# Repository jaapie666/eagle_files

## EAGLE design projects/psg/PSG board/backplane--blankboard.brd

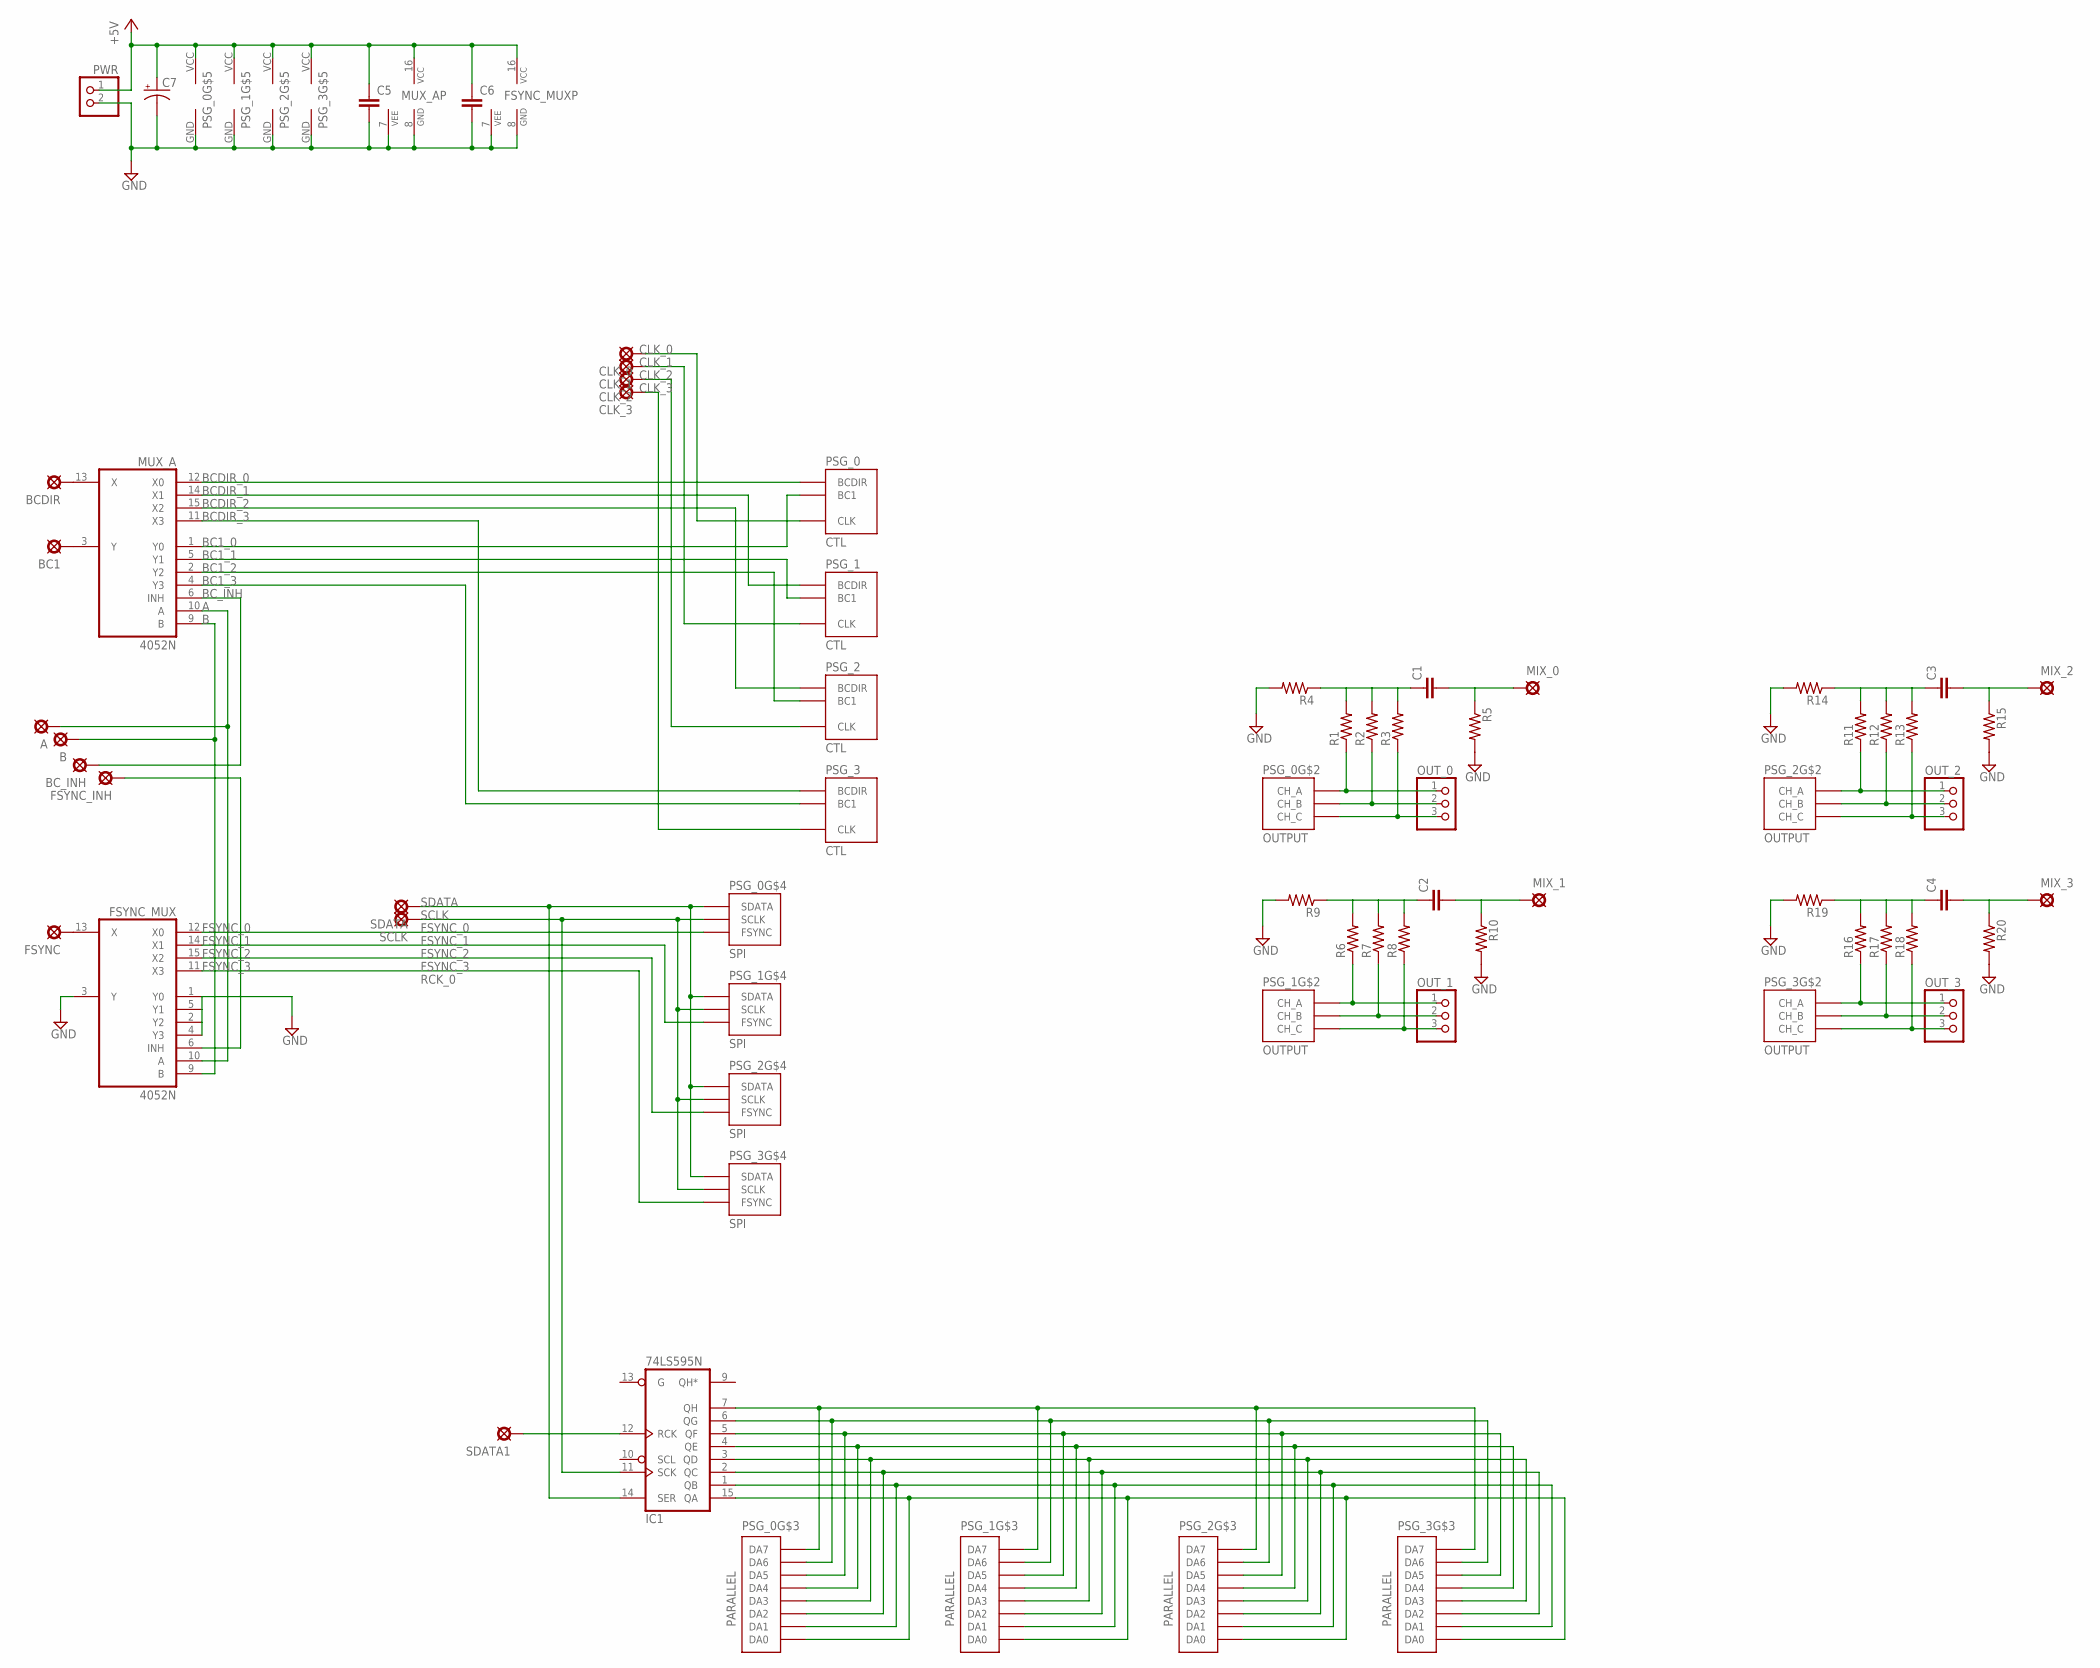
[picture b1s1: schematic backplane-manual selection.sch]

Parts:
A: PAD; SQUARE
B: PAD; SQUARE
BC1: PAD; SQUARE
BCDIR: PAD; SQUARE
BC_INH: PAD; SQUARE
C1, C2, C3, C4: 080X0452; 080X045
C5, C6: 050X030_0251; 050X030_025
C7: 0631; 063_025
CLK_0, CLK_1, CLK_2, CLK_3: PAD; SQUARE
FSYNC: PAD; SQUARE
FSYNC_INH: PAD; SQUARE
FSYNC_MUX: 4052N; DIL16
IC1: 74LS595N; DIL16
MIX_0, MIX_1, MIX_2, MIX_3: PAD; SQUARE
MUX_A: 4052N; DIL16
OUT_0, OUT_1, OUT_2, OUT_3: PINHD-1X3; 1X03
PSG_0, PSG_1, PSG_2, PSG_3: PSG_DAUGHTER
PWR: PINHD-1X2; 1X02
R1, R2, R3, R4, R5, R6, R7, R8, R9, R10, R11, R12, R13, R14, R15, R16, R17, R18, R19, R20: 6MM.3; R0207/3
SCLK: PAD; SQUARE
SDATA, SDATA1: PAD; SQUARE

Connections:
+5V: C5.1, C6.1, C7.+, FSYNC_MUX.16 (VCC), MUX_A.16 (VCC), PSG_0.VCC, PSG_1.VCC, PSG_2.VCC, PSG_3.VCC, PWR.1; also elsewhere on the board
A: A.1, FSYNC_MUX.10 (A), MUX_A.10 (A); also elsewhere on the board
B: B.1, FSYNC_MUX.9 (B), MUX_A.9 (B); also elsewhere on the board
BC1_0: MUX_A.1 (Y0), PSG_0.BC1; also elsewhere on the board
BC1_1: MUX_A.5 (Y1), PSG_1.BC1; also elsewhere on the board
BC1_2: MUX_A.2 (Y2), PSG_2.BC1; also elsewhere on the board
BC1_3: MUX_A.4 (Y3), PSG_3.BC1; also elsewhere on the board
BCDIR_0: MUX_A.12 (X0), PSG_0.BCDIR; also elsewhere on the board
BCDIR_1: MUX_A.14 (X1), PSG_1.BCDIR; also elsewhere on the board
BCDIR_2: MUX_A.15 (X2), PSG_2.BCDIR; also elsewhere on the board
BCDIR_3: MUX_A.11 (X3), PSG_3.BCDIR; also elsewhere on the board
BC_INH: BC_INH.1, MUX_A.6 (INH); also elsewhere on the board
CLK_0: CLK_0.1, PSG_0.CLK
CLK_1: CLK_1.1, PSG_1.CLK
CLK_2: CLK_2.1, PSG_2.CLK
CLK_3: CLK_3.1, PSG_3.CLK
FSYNC: FSYNC.1, FSYNC_MUX.13 (X)
FSYNC_0: FSYNC_MUX.12 (X0), PSG_0.FSYNC
FSYNC_1: FSYNC_MUX.14 (X1), PSG_1.FSYNC
FSYNC_2: FSYNC_MUX.15 (X2), PSG_2.FSYNC
FSYNC_3: FSYNC_MUX.11 (X3), PSG_3.FSYNC
FSYNC_INH: FSYNC_INH.1, FSYNC_MUX.6 (INH)
GND: C5.2, C6.2, C7.-, FSYNC_MUX.1 (Y0), FSYNC_MUX.2 (Y2), FSYNC_MUX.3 (Y), FSYNC_MUX.4 (Y3), FSYNC_MUX.5 (Y1), FSYNC_MUX.7 (VEE), FSYNC_MUX.8 (GND), IC1.8 (GND), MUX_A.7 (VEE), MUX_A.8 (GND), PSG_0.GND, PSG_1.GND, PSG_2.GND, PSG_3.GND, PWR.2, R4.2, R5.2, R9.2, R10.2, R14.2, R15.2, R19.2, R20.2; also elsewhere on the board
unnamed: C1.1, R1.2, R2.2, R3.2, R4.1
unnamed 24: BCDIR.1, MUX_A.13 (X); also elsewhere on the board
unnamed 25: BC1.1, MUX_A.3 (Y); also elsewhere on the board
unnamed: C1.2, MIX_0.1, R5.1
unnamed: C2.1, R6.2, R7.2, R8.2, R9.1
unnamed: C2.2, MIX_1.1, R10.1
unnamed: C3.1, R11.2, R12.2, R13.2, R14.1
unnamed: C3.2, MIX_2.1, R15.1
unnamed 31: IC1.7 (QH), PSG_0.DA7, PSG_1.DA7, PSG_2.DA7, PSG_3.DA7; also elsewhere on the board
unnamed 32: IC1.15 (QA), PSG_0.DA0, PSG_1.DA0, PSG_2.DA0, PSG_3.DA0; also elsewhere on the board
unnamed 33: IC1.1 (QB), PSG_0.DA1, PSG_1.DA1, PSG_2.DA1, PSG_3.DA1; also elsewhere on the board
unnamed 34: IC1.2 (QC), PSG_0.DA2, PSG_1.DA2, PSG_2.DA2, PSG_3.DA2; also elsewhere on the board
unnamed 35: IC1.3 (QD), PSG_0.DA3, PSG_1.DA3, PSG_2.DA3, PSG_3.DA3; also elsewhere on the board
unnamed 36: IC1.4 (QE), PSG_0.DA4, PSG_1.DA4, PSG_2.DA4, PSG_3.DA4; also elsewhere on the board
unnamed 37: IC1.5 (QF), PSG_0.DA5, PSG_1.DA5, PSG_2.DA5, PSG_3.DA5; also elsewhere on the board
unnamed 38: IC1.6 (QG), PSG_0.DA6, PSG_1.DA6, PSG_2.DA6, PSG_3.DA6; also elsewhere on the board
unnamed: OUT_0.1, PSG_0.OUT_A (CH_A), R1.1
unnamed: OUT_0.2, PSG_0.OUT_B (CH_B), R2.1
unnamed: OUT_0.3, PSG_0.OUT_C (CH_C), R3.1
unnamed: OUT_1.1, PSG_1.OUT_A (CH_A), R6.1
unnamed: OUT_1.2, PSG_1.OUT_B (CH_B), R7.1
unnamed: OUT_1.3, PSG_1.OUT_C (CH_C), R8.1
unnamed: OUT_2.1, PSG_2.OUT_A (CH_A), R11.1
unnamed: OUT_2.2, PSG_2.OUT_B (CH_B), R12.1
unnamed: OUT_2.3, PSG_2.OUT_C (CH_C), R13.1
unnamed: OUT_3.1, PSG_3.OUT_A (CH_A), R16.1
unnamed: OUT_3.2, PSG_3.OUT_B (CH_B), R17.1
unnamed: OUT_3.3, PSG_3.OUT_C (CH_C), R18.1
unnamed: C4.1, R16.2, R17.2, R18.2, R19.1
unnamed: C4.2, MIX_3.1, R20.1
RCK_0: IC1.12 (RCK), SDATA1.1
SCLK: IC1.11 (SCK), PSG_0.SCLK, PSG_1.SCLK, PSG_2.SCLK, PSG_3.SCLK, SCLK.1
SDATA: IC1.14 (SER), PSG_0.SDATA, PSG_1.SDATA, PSG_2.SDATA, PSG_3.SDATA, SDATA.1
VCC: IC1.16 (VCC)

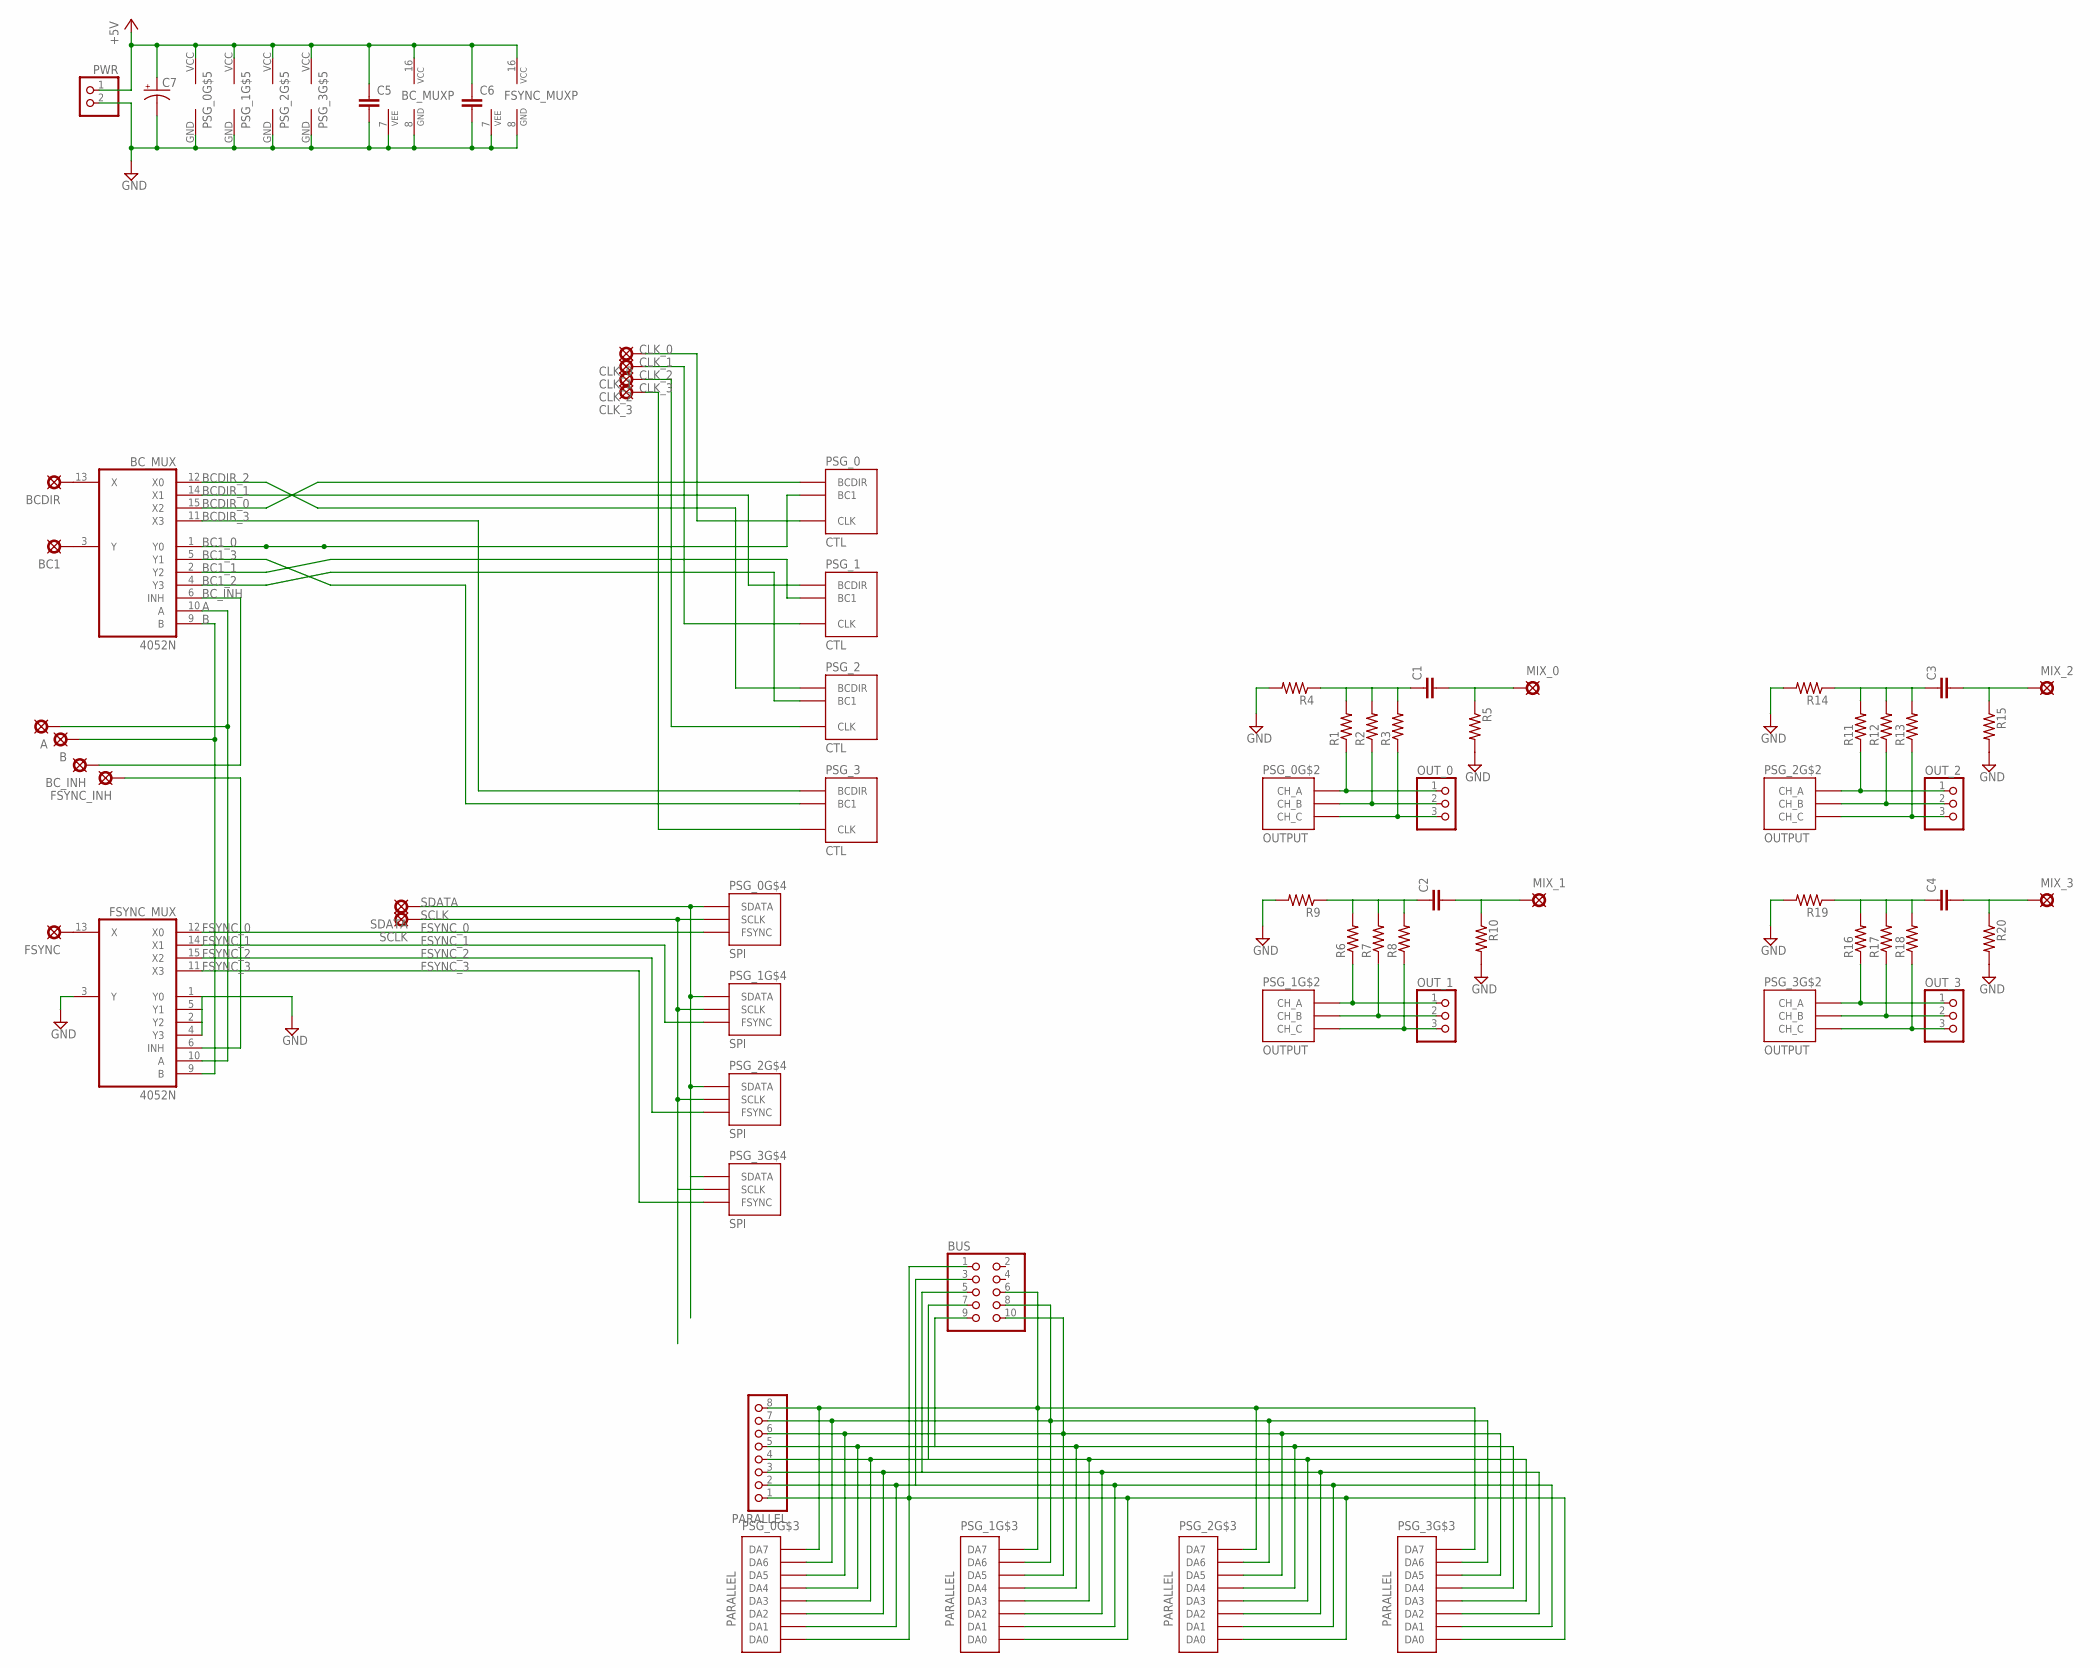
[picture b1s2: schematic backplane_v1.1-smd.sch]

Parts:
A: PAD; SQUARE
B: PAD; SQUARE
BC1: PAD; SQUARE
BCDIR: PAD; SQUARE
BC_INH: PAD; SQUARE
BC_MUX: 4052N; DIL16
BUS: PINHD-2X5IDC; 10PIN_IDC
C1, C2, C3, C4: 070X0302; 070X030
C5, C6: 050X030_0251; 050X030_025
C7: 0631; 063_025
CLK_0, CLK_1, CLK_2, CLK_3: PAD; SQUARE
FSYNC: PAD; SQUARE
FSYNC_INH: PAD; SQUARE
FSYNC_MUX: 4052N; DIL16
MIX_0, MIX_1, MIX_2, MIX_3: PAD; SQUARE
OUT_0, OUT_1, OUT_2, OUT_3: PINHD-1X3; 1X03
PARALLEL: PINHD-1X8; 1X08
PSG_0, PSG_1, PSG_2, PSG_3: PSG_DAUGHTER
PWR: PINHD-1X2; 1X02
R1, R2, R3, R4, R5, R6, R7, R8, R9, R10, R11, R12, R13, R14, R15, R16, R17, R18, R19, R20: 6MM.3; R0207/3
SCLK: PAD; SQUARE
SDATA: PAD; SQUARE

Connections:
+5V: BC_MUX.16 (VCC), C5.1, C6.1, C7.+, FSYNC_MUX.16 (VCC), PSG_0.VCC, PSG_1.VCC, PSG_2.VCC, PSG_3.VCC, PWR.1; also elsewhere on the board
A: A.1, BC_MUX.10 (A), FSYNC_MUX.10 (A); also elsewhere on the board
B: B.1, BC_MUX.9 (B), FSYNC_MUX.9 (B); also elsewhere on the board
BC1_0: BC_MUX.1 (Y0), PSG_0.BC1; also elsewhere on the board
BC1_1: BC_MUX.2 (Y2), PSG_1.BC1; also elsewhere on the board
BC1_2: BC_MUX.4 (Y3), PSG_2.BC1; also elsewhere on the board
BC1_3: BC_MUX.5 (Y1), PSG_3.BC1; also elsewhere on the board
BCDIR_0: BC_MUX.15 (X2), PSG_0.BCDIR; also elsewhere on the board
BCDIR_1: BC_MUX.14 (X1), PSG_1.BCDIR; also elsewhere on the board
BCDIR_2: BC_MUX.12 (X0), PSG_2.BCDIR; also elsewhere on the board
BCDIR_3: BC_MUX.11 (X3), PSG_3.BCDIR; also elsewhere on the board
BC_INH: BC_INH.1, BC_MUX.6 (INH); also elsewhere on the board
CLK_0: CLK_0.1, PSG_0.CLK
CLK_1: CLK_1.1, PSG_1.CLK
CLK_2: CLK_2.1, PSG_2.CLK
CLK_3: CLK_3.1, PSG_3.CLK
FSYNC: FSYNC.1, FSYNC_MUX.13 (X)
FSYNC_0: FSYNC_MUX.12 (X0), PSG_0.FSYNC
FSYNC_1: FSYNC_MUX.14 (X1), PSG_1.FSYNC
FSYNC_2: FSYNC_MUX.15 (X2), PSG_2.FSYNC
FSYNC_3: FSYNC_MUX.11 (X3), PSG_3.FSYNC
FSYNC_INH: FSYNC_INH.1, FSYNC_MUX.6 (INH)
GND: BC_MUX.7 (VEE), BC_MUX.8 (GND), C5.2, C6.2, C7.-, FSYNC_MUX.1 (Y0), FSYNC_MUX.2 (Y2), FSYNC_MUX.3 (Y), FSYNC_MUX.4 (Y3), FSYNC_MUX.5 (Y1), FSYNC_MUX.7 (VEE), FSYNC_MUX.8 (GND), PSG_0.GND, PSG_1.GND, PSG_2.GND, PSG_3.GND, PWR.2, R4.2, R5.2, R9.2, R10.2, R14.2, R15.2, R19.2, R20.2; also elsewhere on the board
unnamed: C1.1, R1.2, R2.2, R3.2, R4.1
unnamed 24: BCDIR.1, BC_MUX.13 (X); also elsewhere on the board
unnamed 25: BC1.1, BC_MUX.3 (Y); also elsewhere on the board
unnamed: C1.2, MIX_0.1, R5.1
unnamed: C2.1, R6.2, R7.2, R8.2, R9.1
unnamed: C2.2, MIX_1.1, R10.1
unnamed: C3.1, R11.2, R12.2, R13.2, R14.1
unnamed: C3.2, MIX_2.1, R15.1
unnamed 31: BUS.6, PARALLEL.8, PSG_0.DA7, PSG_1.DA7, PSG_2.DA7, PSG_3.DA7; also elsewhere on the board
unnamed 32: BUS.1, PARALLEL.1, PSG_0.DA0, PSG_1.DA0, PSG_2.DA0, PSG_3.DA0; also elsewhere on the board
unnamed 33: BUS.3, PARALLEL.2, PSG_0.DA1, PSG_1.DA1, PSG_2.DA1, PSG_3.DA1; also elsewhere on the board
unnamed 34: BUS.5, PARALLEL.3, PSG_0.DA2, PSG_1.DA2, PSG_2.DA2, PSG_3.DA2; also elsewhere on the board
unnamed 35: BUS.7, PARALLEL.4, PSG_0.DA3, PSG_1.DA3, PSG_2.DA3, PSG_3.DA3; also elsewhere on the board
unnamed 36: BUS.9, PARALLEL.5, PSG_0.DA4, PSG_1.DA4, PSG_2.DA4, PSG_3.DA4; also elsewhere on the board
unnamed 37: BUS.10, PARALLEL.6, PSG_0.DA5, PSG_1.DA5, PSG_2.DA5, PSG_3.DA5; also elsewhere on the board
unnamed 38: BUS.8, PARALLEL.7, PSG_0.DA6, PSG_1.DA6, PSG_2.DA6, PSG_3.DA6; also elsewhere on the board
unnamed: OUT_0.1, PSG_0.OUT_A (CH_A), R1.1
unnamed: OUT_0.2, PSG_0.OUT_B (CH_B), R2.1
unnamed: OUT_0.3, PSG_0.OUT_C (CH_C), R3.1
unnamed: OUT_1.1, PSG_1.OUT_A (CH_A), R6.1
unnamed: OUT_1.2, PSG_1.OUT_B (CH_B), R7.1
unnamed: OUT_1.3, PSG_1.OUT_C (CH_C), R8.1
unnamed: OUT_2.1, PSG_2.OUT_A (CH_A), R11.1
unnamed: OUT_2.2, PSG_2.OUT_B (CH_B), R12.1
unnamed: OUT_2.3, PSG_2.OUT_C (CH_C), R13.1
unnamed: OUT_3.1, PSG_3.OUT_A (CH_A), R16.1
unnamed: OUT_3.2, PSG_3.OUT_B (CH_B), R17.1
unnamed: OUT_3.3, PSG_3.OUT_C (CH_C), R18.1
unnamed: C4.1, R16.2, R17.2, R18.2, R19.1
unnamed: C4.2, MIX_3.1, R20.1
SCLK: PSG_0.SCLK, PSG_1.SCLK, PSG_2.SCLK, PSG_3.SCLK, SCLK.1; also elsewhere on the board
SDATA: PSG_0.SDATA, PSG_1.SDATA, PSG_2.SDATA, PSG_3.SDATA, SDATA.1; also elsewhere on the board

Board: 2 copper layers, 57 parts (0 on the bottom side), 56 nets, no tracks yet.

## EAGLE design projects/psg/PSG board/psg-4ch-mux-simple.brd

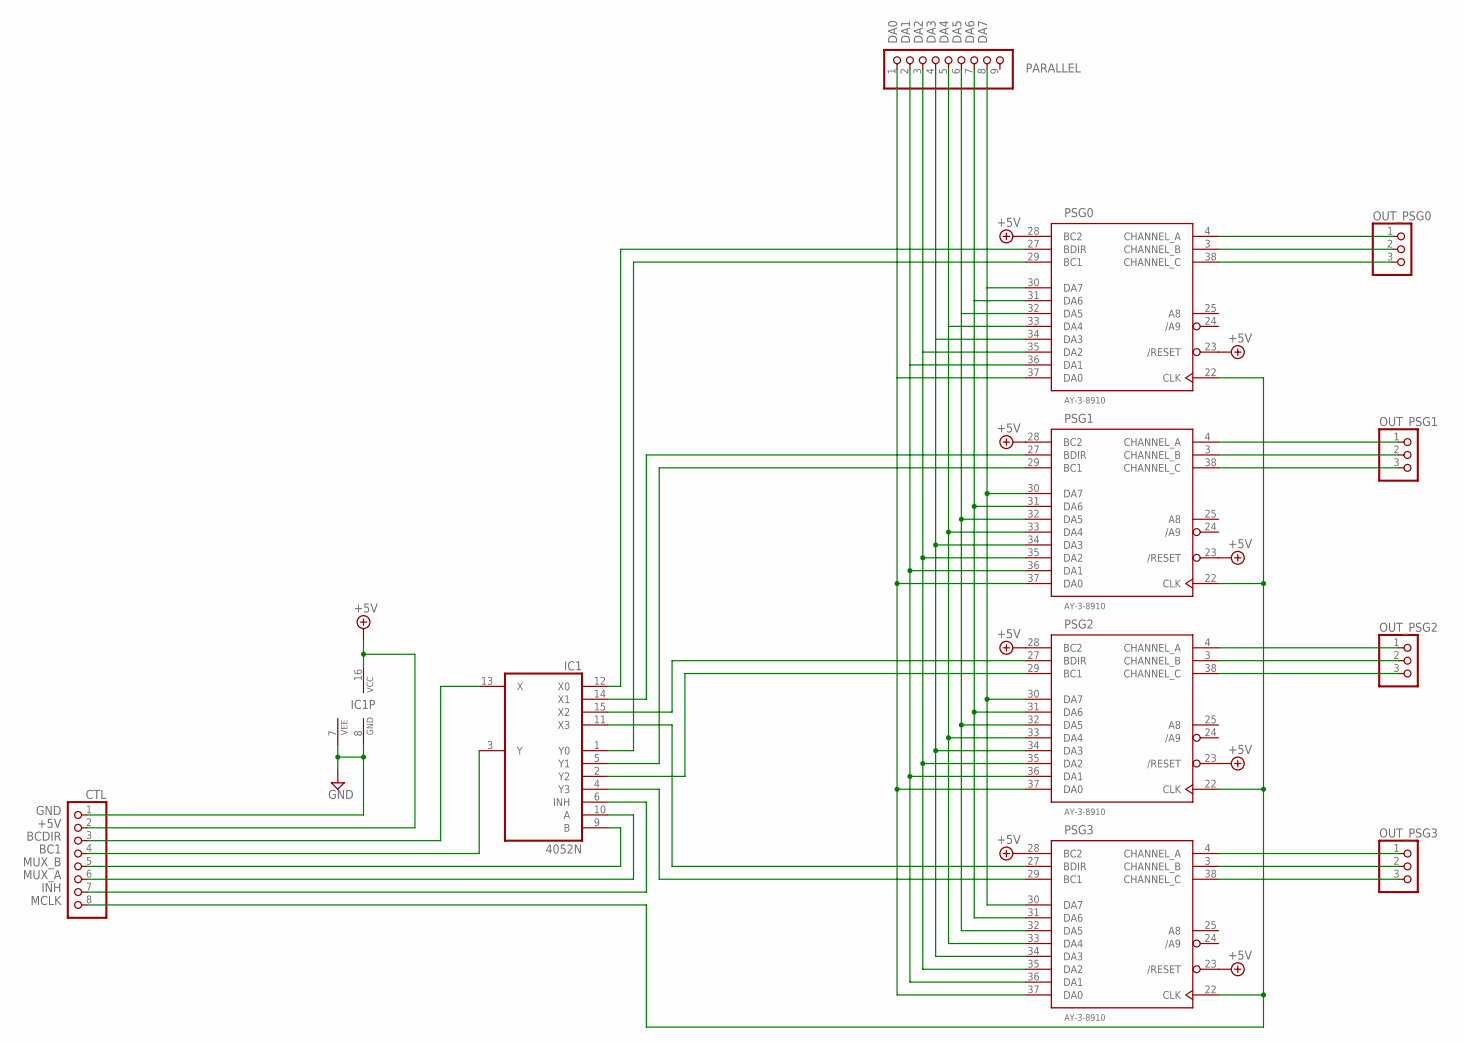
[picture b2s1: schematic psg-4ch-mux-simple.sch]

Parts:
CTL: PINHD-1X8; 1X08
IC1: 4052N; DIL16
OUT_PSG0, OUT_PSG1, OUT_PSG2, OUT_PSG3: PINHD-1X3; 1X03
PARALLEL: PINHD-1X9; 1X09
PSG0, PSG1, PSG2, PSG3: AY-3-8910(2); DIL-40

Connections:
+5V: CTL.2, IC1.16 (VCC), PSG0.23 (/RESET), PSG0.28 (BC2), PSG1.23 (/RESET), PSG1.28 (BC2), PSG2.23 (/RESET), PSG2.28 (BC2), PSG3.23 (/RESET), PSG3.28 (BC2)
+V: PSG0.40 (+V), PSG1.40 (+V), PSG2.40 (+V), PSG3.40 (+V)
BC1: CTL.4, IC1.3 (Y)
BC1_0: IC1.1 (Y0), PSG0.29 (BC1)
BC1_1: IC1.5 (Y1), PSG1.29 (BC1)
BC1_2: IC1.2 (Y2), PSG2.29 (BC1)
BC1_3: IC1.4 (Y3), PSG3.29 (BC1)
BCDIR: CTL.3, IC1.13 (X)
BCDIR_0: IC1.12 (X0), PSG0.27 (BDIR)
BCDIR_1: IC1.14 (X1), PSG1.27 (BDIR)
BCDIR_2: IC1.15 (X2), PSG2.27 (BDIR)
BCDIR_3: IC1.11 (X3), PSG3.27 (BDIR)
DA0: PARALLEL.1, PSG0.37 (DA0)
DA1: PARALLEL.2, PSG0.36 (DA1)
DA2: PARALLEL.3, PSG0.35 (DA2)
DA3: PARALLEL.4, PSG0.34 (DA3)
DA4: PARALLEL.5, PSG0.33 (DA4)
DA5: PARALLEL.6, PSG0.32 (DA5)
DA6: PARALLEL.7, PSG0.31 (DA6)
DA7: PARALLEL.8, PSG0.30 (DA7)
DA8: PSG3.37 (DA0)
DA9: PSG3.36 (DA1)
DA10: PSG3.35 (DA2)
DA11: PSG3.34 (DA3)
DA12: PSG3.33 (DA4)
DA13: PSG3.32 (DA5)
DA14: PSG3.31 (DA6)
DA15: PSG3.30 (DA7)
GND: CTL.1, IC1.7 (VEE), IC1.8 (GND), PSG0.1 (GND), PSG1.1 (GND), PSG2.1 (GND), PSG3.1 (GND)
INH: CTL.7, IC1.6 (INH)
MCLK: CTL.8, PSG0.22 (CLK), PSG1.22 (CLK), PSG2.22 (CLK), PSG3.22 (CLK)
MUX_A: CTL.6, IC1.10 (A)
MUX_B: CTL.5, IC1.9 (B)
unnamed: OUT_PSG0.1, PSG0.4 (CHANNEL_A)
unnamed: OUT_PSG0.2, PSG0.3 (CHANNEL_B)
unnamed: OUT_PSG0.3, PSG0.38 (CHANNEL_C)
unnamed: OUT_PSG1.1, PSG1.4 (CHANNEL_A)
unnamed: OUT_PSG1.2, PSG1.3 (CHANNEL_B)
unnamed: OUT_PSG1.3, PSG1.38 (CHANNEL_C)
unnamed: OUT_PSG2.1, PSG2.4 (CHANNEL_A)
unnamed: OUT_PSG2.2, PSG2.3 (CHANNEL_B)
unnamed: OUT_PSG2.3, PSG2.38 (CHANNEL_C)
unnamed: OUT_PSG3.1, PSG3.4 (CHANNEL_A)
unnamed: OUT_PSG3.2, PSG3.3 (CHANNEL_B)
unnamed: OUT_PSG3.3, PSG3.38 (CHANNEL_C)

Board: 2 copper layers, 11 parts (0 on the bottom side), 37 nets, no tracks yet.

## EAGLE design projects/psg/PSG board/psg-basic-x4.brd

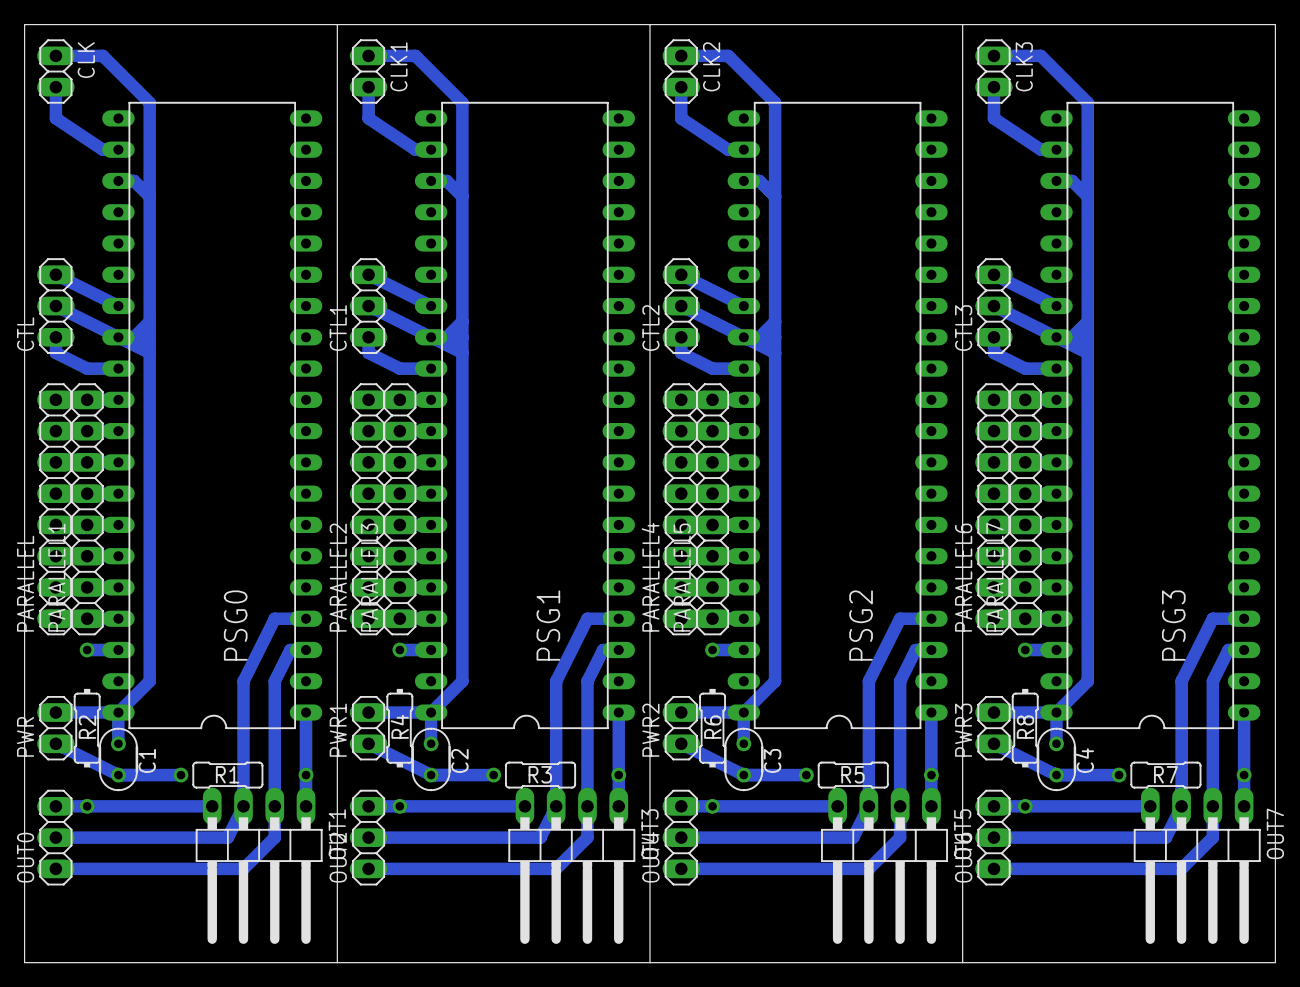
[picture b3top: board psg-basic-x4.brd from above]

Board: 2 copper layers, 101.6 x 76.2 mm, 44 parts (0 on the bottom side), 72 nets.

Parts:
C1, C2, C3, C4: 100n; 050X030_025
CLK, CLK1, CLK2, CLK3: 1X02
CTL, CTL1, CTL2, CTL3: 1X03
OUT0, OUT2, OUT4, OUT6: 1X03
OUT1, OUT3, OUT5, OUT7: 1X04/90
PARALLEL, PARALLEL1, PARALLEL2, PARALLEL3, PARALLEL4, PARALLEL5, PARALLEL6, PARALLEL7: 1X08
PSG0, PSG1, PSG2, PSG3: DIL40
PWR, PWR1, PWR2, PWR3: 1X02
R1, R3, R5, R7: R0207/4A
R2, R4, R6, R8: R0207/5

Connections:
+5V: C1.1, CLK.1, CTL.2, PSG0.23, PSG0.28, PSG0.40, PWR.2
+5V1: C2.1, CLK1.1, CTL1.2, PSG1.23, PSG1.28, PSG1.40, PWR1.2
+5V2: C3.1, CLK2.1, CTL2.2, PSG2.23, PSG2.28, PSG2.40, PWR2.2
+5V3: C4.1, CLK3.1, CTL3.2, PSG3.23, PSG3.28, PSG3.40, PWR3.2
BC1: CTL.1, PSG0.29
BC2: CTL1.1, PSG1.29
BC3: CTL2.1, PSG2.29
BC4: CTL3.1, PSG3.29
BCDIR: CTL.3, PSG0.27
BCDIR1: CTL1.3, PSG1.27
BCDIR2: CTL2.3, PSG2.27
BCDIR3: CTL3.3, PSG3.27
DA0: PARALLEL.1, PARALLEL1.1, PSG0.37
DA1: PARALLEL.2, PARALLEL1.2, PSG0.36
DA2: PARALLEL.3, PARALLEL1.3, PSG0.35
DA3: PARALLEL.4, PARALLEL1.4, PSG0.34
DA4: PARALLEL.5, PARALLEL1.5, PSG0.33
DA5: PARALLEL.6, PARALLEL1.6, PSG0.32
DA6: PARALLEL.7, PARALLEL1.7, PSG0.31
DA7: PARALLEL.8, PARALLEL1.8, PSG0.30
DA8: PARALLEL2.8, PARALLEL3.8, PSG1.30
DA9: PARALLEL2.7, PARALLEL3.7, PSG1.31
DA10: PARALLEL2.6, PARALLEL3.6, PSG1.32
DA11: PARALLEL2.5, PARALLEL3.5, PSG1.33
DA12: PARALLEL2.4, PARALLEL3.4, PSG1.34
DA13: PARALLEL2.3, PARALLEL3.3, PSG1.35
DA14: PARALLEL2.2, PARALLEL3.2, PSG1.36
DA15: PARALLEL2.1, PARALLEL3.1, PSG1.37
DA16: PARALLEL4.8, PARALLEL5.8, PSG2.30
DA17: PARALLEL4.7, PARALLEL5.7, PSG2.31
DA18: PARALLEL4.6, PARALLEL5.6, PSG2.32
DA19: PARALLEL4.5, PARALLEL5.5, PSG2.33
DA20: PARALLEL4.4, PARALLEL5.4, PSG2.34
DA21: PARALLEL4.3, PARALLEL5.3, PSG2.35
DA22: PARALLEL4.2, PARALLEL5.2, PSG2.36
DA23: PARALLEL4.1, PARALLEL5.1, PSG2.37
DA24: PARALLEL6.8, PARALLEL7.8, PSG3.30
DA25: PARALLEL6.7, PARALLEL7.7, PSG3.31
DA26: PARALLEL6.6, PARALLEL7.6, PSG3.32
DA27: PARALLEL6.5, PARALLEL7.5, PSG3.33
DA28: PARALLEL6.4, PARALLEL7.4, PSG3.34
DA29: PARALLEL6.3, PARALLEL7.3, PSG3.35
DA30: PARALLEL6.2, PARALLEL7.2, PSG3.36
DA31: PARALLEL6.1, PARALLEL7.1, PSG3.37
GND: C1.2, PWR.1, R1.1
GND1: C2.2, PWR1.1, R3.1
GND2: C3.2, PWR2.1, R5.1
GND3: C4.2, PWR3.1, R7.1
unnamed: CLK1.2, PSG1.22
unnamed: OUT2.3, OUT3.4, R4.2
unnamed: PSG0.38, R2.1
unnamed: OUT0.3, OUT1.4, R2.2
unnamed: CLK.2, PSG0.22
unnamed: OUT0.2, OUT1.3, PSG0.4
unnamed: OUT0.1, OUT1.2, PSG0.3
unnamed: OUT1.1, PSG0.1, R1.2
unnamed: OUT2.2, OUT3.3, PSG1.4
unnamed: OUT2.1, OUT3.2, PSG1.3
unnamed: OUT3.1, PSG1.1, R3.2
unnamed: PSG1.38, R4.1
unnamed: CLK2.2, PSG2.22
unnamed: OUT4.3, OUT5.4, R6.2
unnamed: OUT4.2, OUT5.3, PSG2.4
unnamed: OUT4.1, OUT5.2, PSG2.3
unnamed: OUT5.1, PSG2.1, R5.2
unnamed: PSG2.38, R6.1
unnamed: CLK3.2, PSG3.22
unnamed: OUT6.3, OUT7.4, R8.2
unnamed: OUT6.2, OUT7.3, PSG3.4
unnamed: OUT6.1, OUT7.2, PSG3.3
unnamed: OUT7.1, PSG3.1, R7.2
unnamed: PSG3.38, R8.1
